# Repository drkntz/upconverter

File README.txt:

README:
This circuit up-converts from a little bit above DC to ~25MHz to VHF. Its intended use is with an RTL-SDR. 
It requires the program Kicad to view and edit.
Created in 2020 by Zach Martin, 
Added to git in August 2020, pushed to github Aug 13 2020.

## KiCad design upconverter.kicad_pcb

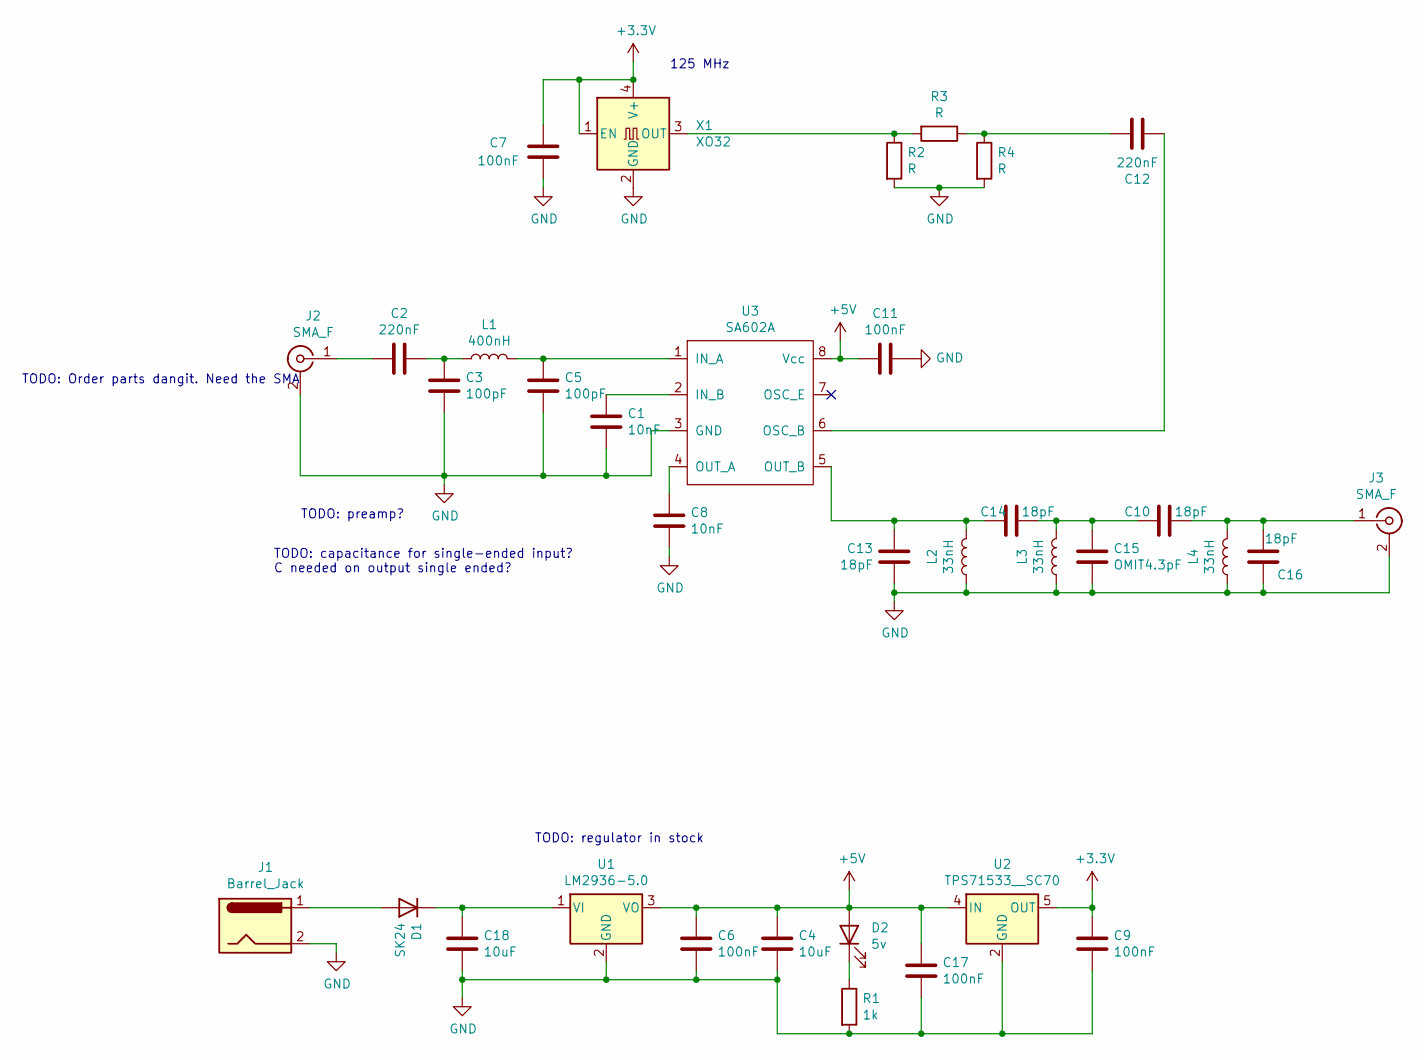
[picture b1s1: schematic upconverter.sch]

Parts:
C1, C8: 10nF; C_0603_1608Metric
C2, C12: 220nF; C_0805_2012Metric
C3, C5: 100pF; C_0603_1608Metric
C4, C18: 10uF; C_0805_2012Metric
C6, C7, C9, C11, C17: 100nF; C_0805_2012Metric
C10, C16: 18pF; C_0805_2012Metric
C13, C14: 18pF; C_0603_1608Metric
C15: OMIT4.3pF; C_0603_1608Metric
D1: SK24; D_SMB
D2: 5v; LED_D3.0mm
J1: Barrel_Jack; PJ-002A_2.1_5.5_Barrel_Jack_CUI
J2, J3: SMA_F; SMA_Amphenol_901-144_Vertical
L1: 400nH; L_0805_2012Metric
L2, L3, L4: 33nH; L_0805_2012Metric
R1: 1k; R_0805_2012Metric
R2, R3, R4: R; R_0603_1608Metric
U1: LM2936-5.0; SOT-89-3
U2: TPS71533__SC70; SOT-353_SC-70-5
U3: SA602A; SO-8_3.9x4.9mm_P1.27mm
X1: XO32; Oscillator_SMD_IDT_JU6-6_7.0x5.0mm_P2.54mm

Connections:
+3V3: C7.1, C9.1, U2.5 (OUT), X1.1 (EN), X1.4 (V+)
+5V: C4.1, C6.1, C11.2, C17.1, D2.2 (A), U1.3 (VO), U2.4 (IN), U3.8 (Vcc)
GND: C1.2, C3.2, C4.2, C5.2, C6.2, C7.2, C8.2, C9.2, C11.1, C13.1, C15.2, C16.1, C17.2, C18.2, J1.2, J2.2 (Ext), J3.2 (Ext), L2.1, L3.1, L4.1, R1.2, R2.2, R4.2, U1.2 (GND), U2.2 (GND), U3.3 (GND), X1.2 (GND)
unnamed: C1.1, U3.2 (IN_B)
unnamed: C2.1, C3.1, L1.1
unnamed: C2.2, J2.1 (In)
unnamed: C5.1, L1.2, U3.1 (IN_A)
unnamed: C8.1, U3.4 (OUT_A)
unnamed: C10.1, C14.1, C15.1, L3.2
unnamed: C10.2, C16.2, J3.1 (In), L4.2
unnamed: C12.1, R3.1, R4.1
unnamed: C12.2, U3.6 (OSC_B)
unnamed: C13.2, C14.2, L2.2, U3.5 (OUT_B)
unnamed: C18.1, D1.1 (K), U1.1 (VI)
unnamed: D1.2 (A), J1.1
unnamed: D2.1 (K), R1.1
unnamed: R2.1, R3.2, X1.3 (OUT)

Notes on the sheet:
TODO: preamp?
125 MHz
TODO: capacitance for single-ended input? C needed on output single ended?
TODO: Order parts dangit. Need the SMA
TODO: regulator in stock

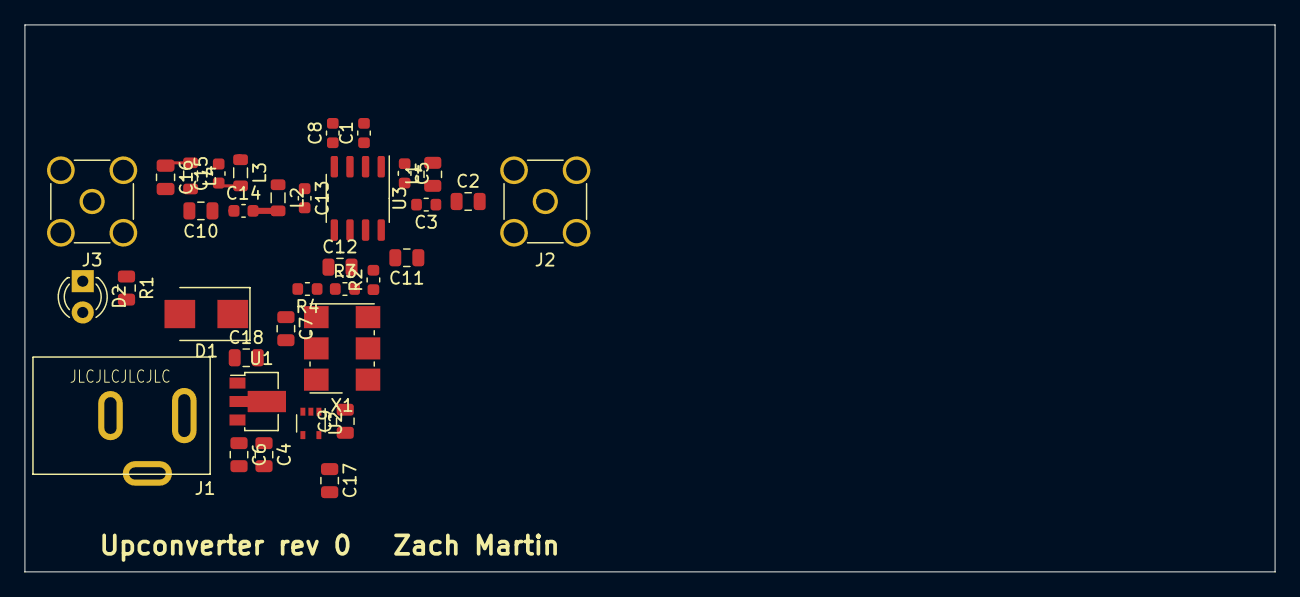
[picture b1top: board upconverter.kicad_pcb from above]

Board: 2 copper layers, 101.6 x 44.5 mm, 35 parts (0 on the bottom side), 17 nets.

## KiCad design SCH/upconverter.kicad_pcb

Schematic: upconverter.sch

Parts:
C1, C3, C10: 100nF; C_Disc_D6.0mm_W2.5mm_P5.00mm
C2, C7: 220uF; CP_Radial_D10.0mm_P5.00mm
C4, C6, C8, C9: 100pF; C_Disc_D3.0mm_W2.0mm_P2.50mm
C5, C11, C12: 220nF; C_Disc_D7.5mm_W4.4mm_P5.00mm
D1: 3.3v; D_5KPW_P7.62mm_Vertical_AnodeUp
D2: 1N4007; D_DO-41_SOD81_P10.16mm_Horizontal
D3: 5v; LED_D5.0mm
D4: 5v; D_5KPW_P7.62mm_Vertical_AnodeUp
D5: LED; LED_D5.0mm
J1: Barrel_Jack; BarrelJack_CUI_PJ-102AH_Horizontal
J3, J5: SMA_F; SMA_Amphenol_901-144_Vertical
J4: USB_B_Mini; USB_Mini-B_Wuerth_65100516121_Horizontal
L3, L4: 400nH; L_Axial_L12.8mm_D5.8mm_P25.40mm_Horizontal_Fastron_HBCC
R1, R5: 1k; R_Axial_DIN0207_L6.3mm_D2.5mm_P10.16mm_Horizontal
R2, R3, R4: R; R_Axial_DIN0207_L6.3mm_D2.5mm_P10.16mm_Horizontal
R6: 470R; R_Axial_DIN0207_L6.3mm_D2.5mm_P10.16mm_Horizontal
U2: SA602A; SO-8_3.9x4.9mm_P1.27mm
X1: XO32; Oscillator_SMD_EuroQuartz_XO32-4Pin_3.2x2.5mm

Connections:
+3V3: C1.1, C2.1, D1.1, D5.2 (A), R5.1, X1.1 (EN), X1.4 (V+)
+5V: C3.2, C7.1, D2.1 (K), D3.2 (A), D4.1, J4.1, R5.2, U2.8 (Vcc)
GND: C1.2, C2.2, C3.1, C4.2, C6.2, C7.2, C8.2, C9.2, C10.2, D1.2, D4.2, J1.2, J3.2 (Ext), J4.5, J4.6, J5.2 (Ext), R1.2, R2.2, R4.2, R6.2, U2.3 (GND), X1.2 (GND)
unnamed: C4.1, C8.1, L3.2, L4.1
unnamed: C5.1, C6.1, L3.1
unnamed: C5.2, J3.1 (In)
unnamed: C9.1, L4.2, U2.1 (IN_A)
unnamed: C10.1, U2.2 (IN_B)
unnamed: C11.1, J5.1 (In)
unnamed: C11.2, U2.4 (OUT_A)
unnamed: C12.1, R3.1, R4.1
unnamed: C12.2, U2.7 (OSC_E)
unnamed: D2.2 (A), J1.1
unnamed: D3.1 (K), R1.1
unnamed: D5.1 (K), R6.1
unnamed: R2.1, R3.2, X1.3 (OUT)

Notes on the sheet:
Note: Zener may cause psu noise in its attempt to regulate to 3.3v, hence the output cap. I don't think the values are that critical
is 5v zener on the input a good way to ensure a high voltage like 12v doesn't get put on the input?
Just spitballing on this cap -->

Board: 2 copper layers, 31 parts (0 on the bottom side), 16 nets, no tracks yet.

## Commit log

2020-08-14 Updates to psu
2020-08-14 Added Readme
2020-08-17 Updated Schematic, removed SBL-1 version, added footprints, and started on layout.
2020-08-21 Re-organized and added pdf of schematic
2020-09-30 Latest version before updating PC
2021-07-20 Changed filter, added matching xformers, changed power supplies to 7805 and 3.3v LDO
2021-07-20 Updated footprints, transformer
2021-07-21 started layout, footprints on new changes
2021-07-21 input LPF
2021-07-21 Updated output filter
2021-07-21 Board edge, tracks. Need to finish DRC fixes & JLCPCB setup
2021-08-03 gerbers
2021-08-12 Updated schematic for experimental single-ended input/output. TODO: test if it works, test i/o characteristics. Note impedance issue vs balun
2021-08-12 Layout for single ended vers. TODO:needs silk screen text, fix ref des, lay tracks/fills, board size, TESTTT
